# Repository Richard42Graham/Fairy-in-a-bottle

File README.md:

# Fairy-in-a-bottle
Some cool fairy lighting in a bottole.

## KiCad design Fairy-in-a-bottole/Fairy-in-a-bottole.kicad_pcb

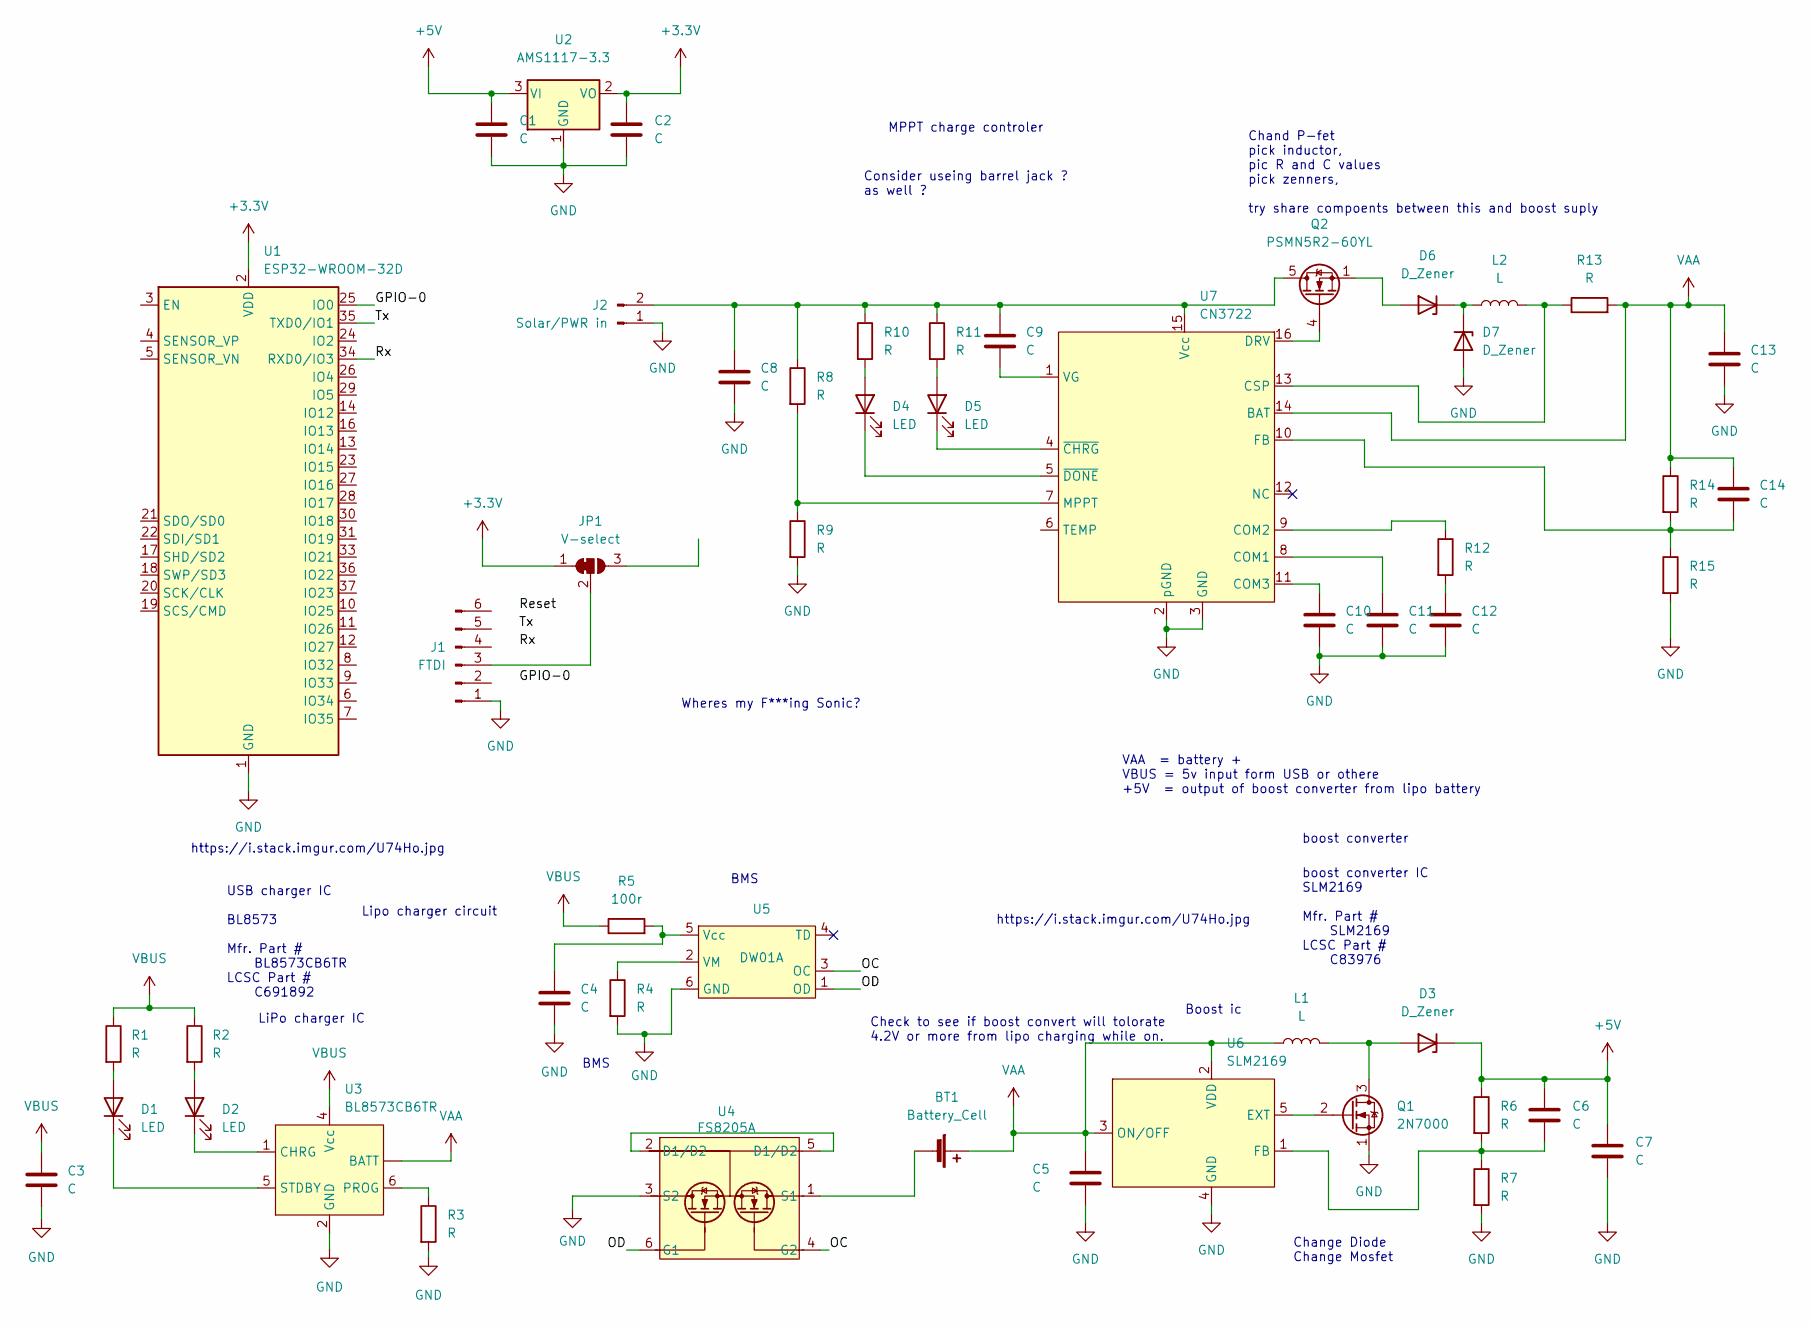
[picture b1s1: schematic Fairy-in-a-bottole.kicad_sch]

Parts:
BT1: Battery_Cell; BatteryHolder_Keystone_1042_1x18650
C1, C2: C; C_0805_2012Metric
C3, C4, C5, C6, C7, C8, C9, C10, C11, C12, C13, C14: C; C_0805_2012Metric_Pad1.18x1.45mm_HandSolder
D1, D2, D4, D5: LED; D_3220_8050Metric_Pad2.65x5.15mm_HandSolder
D3: D_Zener
D6, D7: D_Zener; D_1210_3225Metric
J1: FTDI; PinSocket_1x06_P2.54mm_Vertical
J2: Solar/PWR in; PinSocket_1x02_P2.54mm_Vertical
JP1: V-select; SolderJumper-3_P1.3mm_Bridged2Bar12_Pad1.0x1.5mm_NumberLabe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
L1: L
L2: L; L_12x12mm_H8mm
Q1: 2N7000; TO-92_Inline
Q2: PSMN5R2-60YL; LFPAK56
R1, R2, R3, R4, R6, R7, R8, R9, R10, R11, R12, R13, R14, R15: R; R_0603_1608Metric
R5: 100r; R_0603_1608Metric
U1: ESP32-WROOM-32D; ESP32-WROOM-32
U2: AMS1117-3.3; SOT-223-3_TabPin2
U3: BL8573CB6TR; SOT-23-6
U4: FS8205A; SOT-23-6
U5: DW01A; SOT-23-6
U6: SLM2169; SOT-23-5
U7: CN3722; TSSOP-16_4.4x5mm_P0.65mm

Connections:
+3.3V: C2.1, JP1.1 (A), U1.2 (VDD), U2.2 (VO)
+5V: C1.1, C6.1, C7.1, D3.1 (K), R6.1, U2.3 (VI)
/GPIO-0: U1.25 (IO0)
/OC: U4.4 (G2), U5.3 (OC)
/OD: U4.6 (G1), U5.1 (OD)
/Rx: U1.34 (RXD0/IO3)
/Tx: U1.35 (TXD0/IO1)
GND: C1.2, C2.2, C3.2, C4.2, C5.2, C7.2, C8.2, C10.2, C11.2, C12.2, C13.2, D7.2 (A), J1.1, J2.1, Q1.1 (S), R3.2, R4.2, R7.2, R9.2, R15.2, U1.1 (GND), U1.15 (GND), U1.38 (GND), U1.39 (GND), U2.1 (GND), U3.2 (GND), U4.3 (S2), U5.6 (GND), U6.4 (GND), U7.2 (pGND), U7.3 (GND)
unnamed: BT1.2 (-), U4.1 (S1)
unnamed: C4.1, R5.2, U5.5 (Vcc)
unnamed: C6.2, R6.2, R7.1, U6.1 (FB)
unnamed: C8.1, C9.1, J2.2, Q2.5 (D), R8.1, R10.1, R11.1, U7.15 (Vcc)
unnamed: C9.2, U7.1 (VG)
unnamed: C10.1, U7.11 (COM3)
unnamed: C11.1, U7.8 (COM1)
unnamed: C12.1, R12.2
unnamed: C14.2, R14.2, R15.1, U7.10 (FB)
unnamed: D1.1 (K), U3.5 (STDBY)
unnamed: D1.2 (A), R1.2
unnamed: D2.1 (K), U3.1 (CHRG)
unnamed: D2.2 (A), R2.2
unnamed: D3.2 (A), L1.2, Q1.3 (D)
unnamed: D4.1 (K), U7.5 (~DONE)
unnamed: D4.2 (A), R10.2
unnamed: D5.1 (K), U7.4 (~CHRG)
unnamed: D5.2 (A), R11.2
unnamed: D6.1 (K), D7.1 (K), L2.1
unnamed: D6.2 (A), Q2.1 (S), Q2.2 (S), Q2.3 (S)
unnamed: J1.3, JP1.2 (C)
unnamed: L2.2, R13.1, U7.13 (CSP)
unnamed: Q1.2 (G), U6.5 (EXT)
unnamed: Q2.4 (G), U7.16 (DRV)
unnamed: R3.1, U3.6 (PROG)
unnamed: R4.1, U5.2 (VM)
unnamed: R8.2, R9.1, U7.7 (MPPT)
unnamed: R12.1, U7.9 (COM2)
unnamed: U4.2 (D1/D2), U4.5 (D1/D2)
VAA: BT1.1 (+), C5.1, C13.1, C14.1, L1.1, R13.2, R14.1, U3. (BATT), U6.2 (VDD), U6.3 (ON/OFF), U7.14 (BAT)
VBUS: C3.1, R1.1, R2.1, R5.1, U3.4 (Vcc)

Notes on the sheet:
Wheres my F***ing Sonic?
LiPo charger IC
USB charger IC BL8573 Mfr. Part # BL8573CB6TR LCSC Part # C691892
Chand P-fet pick inductor, pic R and C values pick zenners, try share compoents between this and boost suply
Check to see if boost convert will tolorate 4.2V or more from lipo charging while on.
boost converter IC SLM2169 Mfr. Part # SLM2169 LCSC Part # C83976
MPPT charge controler
BMS
Boost ic
Lipo charger circuit
VAA = battery + VBUS = 5v input form USB or othere +5V = output of boost converter from lipo battery
https://i.stack.imgur.com/U74Ho.jpg
boost converter
Change Diode Change Mosfet
Consider useing barrel jack ? as well ?

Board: 2 copper layers, 49 parts (0 on the bottom side), 35 nets, no tracks yet.

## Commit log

2022-08-11 added the first parts of the schmatic and such :3
2022-08-16 added link to usefull battery proection cirucit
2022-08-21 added some parts to it dude
2022-08-22 updated scimatic symbols as they were on the wrong grid size :/ and wired in a lose ciruit for how it should work, still gotta check stuff.
2022-08-23 added footprints for the most components
2022-08-29 added MPTT part and some footprints, and comments
2022-08-29 asigned foorprints and populated the pcb with them
2022-08-29 Added sketches of design and pesto jar dimensions
2022-10-26 just adding some notes
